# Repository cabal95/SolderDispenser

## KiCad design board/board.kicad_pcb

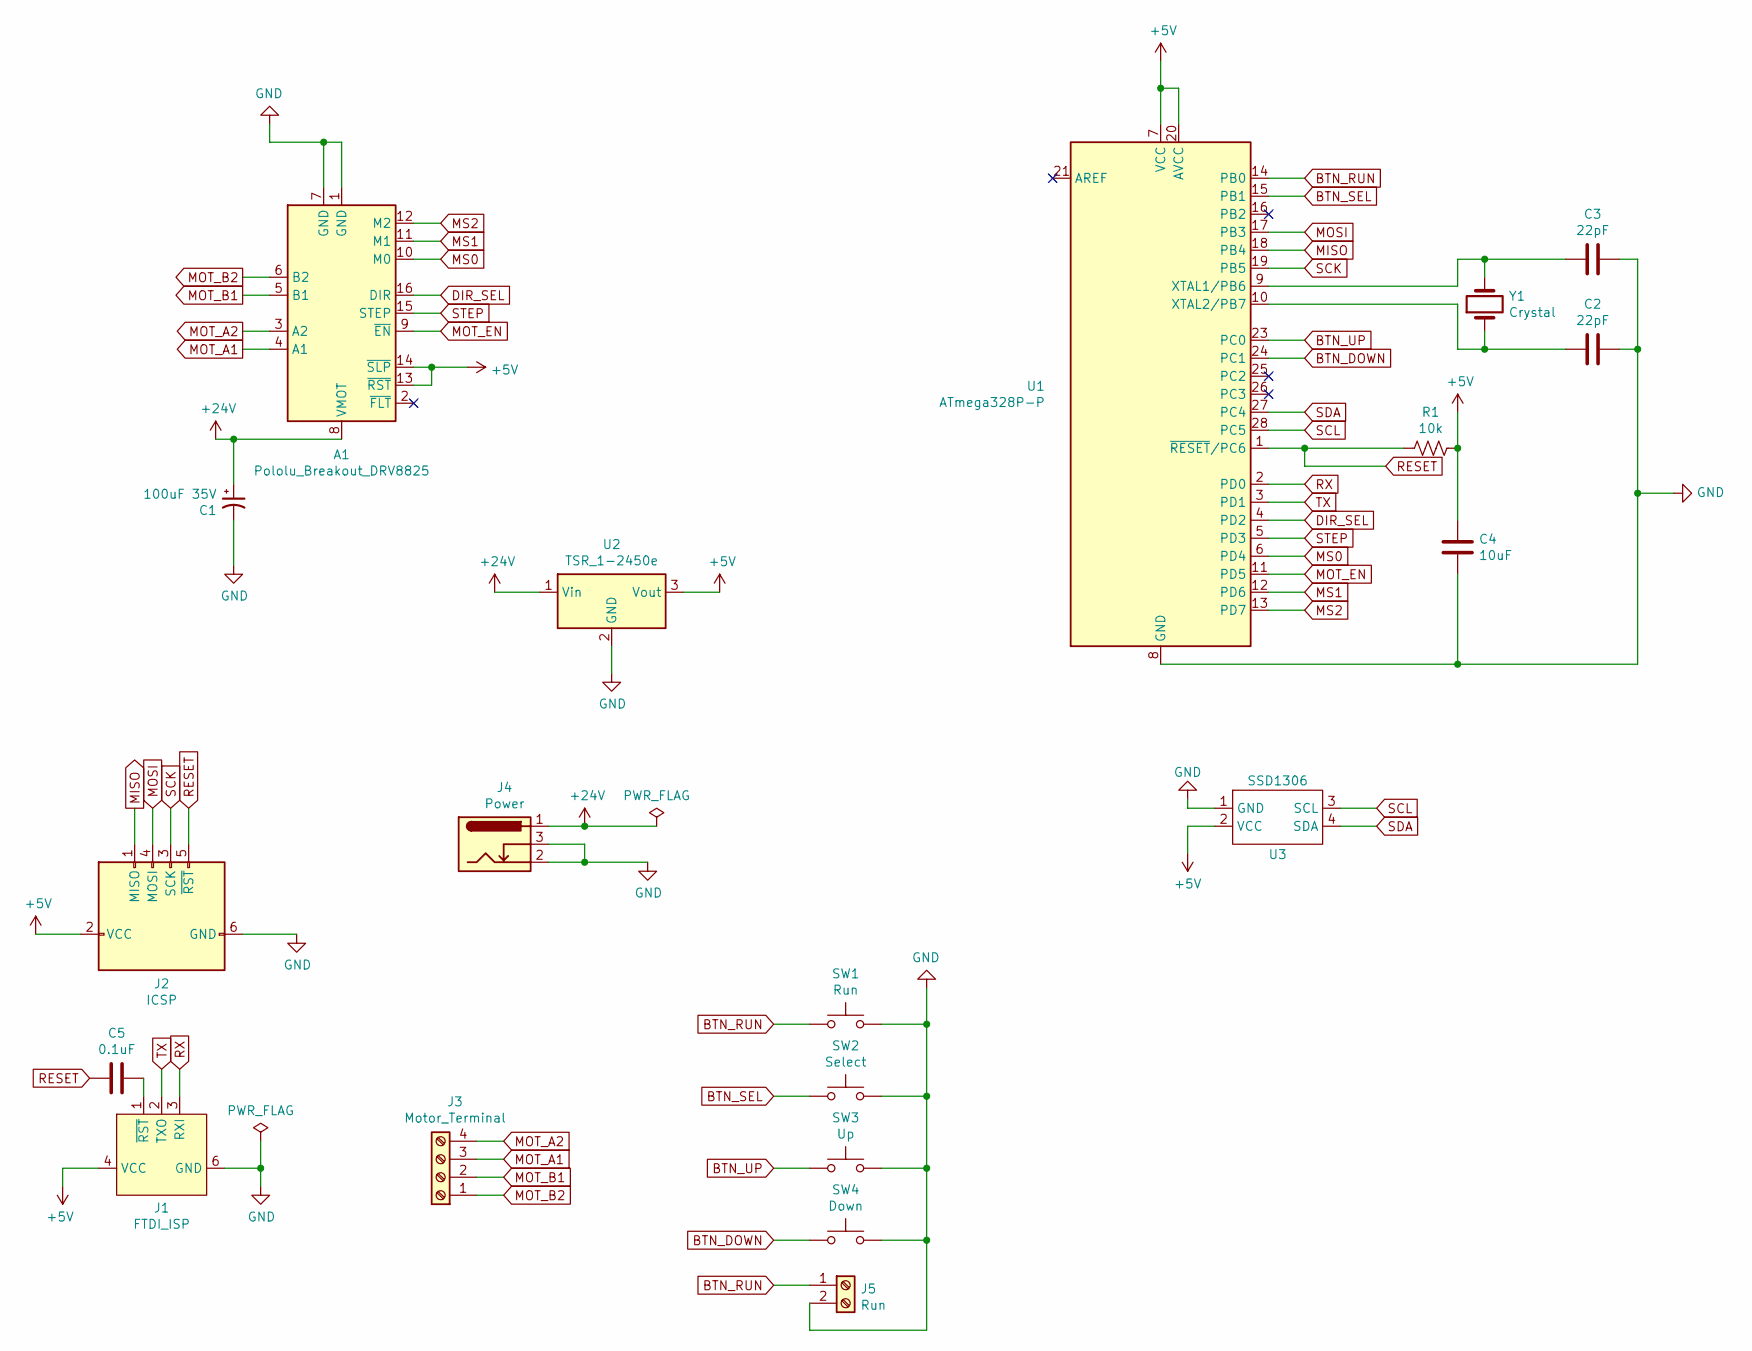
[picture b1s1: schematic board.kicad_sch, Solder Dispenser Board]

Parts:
A1: Pololu_Breakout_DRV8825; Pololu_Breakout-16_15.2x20.3mm
C1: 100uF 35V; CP_Radial_D6.3mm_P2.50mm
C2, C3: 22pF; C_Disc_D6.0mm_W2.5mm_P5.00mm
C4: 10uF; CP_Radial_D5.0mm_P2.00mm
C5: 0.1uF; C_Disc_D3.4mm_W2.1mm_P2.50mm
J1: FTDI_ISP; PinHeader_1x06_P2.54mm_Vertical
J2: ICSP; PinHeader_2x03_P2.54mm_Vertical
J3: Motor_Terminal; TerminalBlock_Phoenix_MKDS-1,5-4-5.08_1x04_P5.08mm_Horizont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
J4: Power; BarrelJack_Horizontal
J5: Run; TerminalBlock_Phoenix_MKDS-1,5-2-5.08_1x02_P5.08mm_Horizont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
R1: 10k; R_Axial_DIN0207_L6.3mm_D2.5mm_P10.16mm_Horizontal
SW1: Run; SW_PUSH_6mm_H5mm
SW2: Select; SW_PUSH_6mm_H5mm
SW3: Up; SW_PUSH_6mm_H5mm
SW4: Down; SW_PUSH_6mm_H5mm
U1: ATmega328P-P; DIP-28_W7.62mm
U2: TSR_1-2450e; Converter_DCDC_TRACO_TSR-1_THT
U3: SSD1306; PinHeader_1x04_P2.54mm_Vertical
Y1: Crystal; Crystal_HC49-U_Vertical

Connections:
+5V: A1.13 (~RST), A1.14 (~SLP), C4.1, J1.4 (VCC), J2.2 (VCC), R1.2, U1.7 (VCC), U1.20 (AVCC), U2.3 (Vout), U3.2 (VCC)
+24V: A1.8 (VMOT), C1.1, J4.1, U2.1 (Vin)
BTN_DOWN: SW4.1, U1.24 (PC1)
BTN_RUN: J5.1, SW1.1, U1.14 (PB0)
BTN_SEL: SW2.1, U1.15 (PB1)
BTN_UP: SW3.1, U1.23 (PC0)
DIR_SEL: A1.16 (DIR), U1.4 (PD2)
GND: A1.1 (GND), A1.7 (GND), C1.2, C2.2, C3.2, C4.2, J1.6 (GND), J2.6 (GND), J4.2, J4.3, J5.2, SW1.2, SW2.2, SW3.2, SW4.2, U1.8 (GND), U1.22 (GND), U2.2 (GND), U3.1 (GND)
MISO: J2.1 (MISO), U1.18 (PB4)
MOSI: J2.4 (MOSI), U1.17 (PB3)
MOT_A1: A1.4 (A1), J3.3
MOT_A2: A1.3 (A2), J3.4
MOT_B1: A1.5 (B1), J3.2
MOT_B2: A1.6 (B2), J3.1
MOT_EN: A1.9 (~EN), U1.11 (PD5)
MS0: A1.10 (M0), U1.6 (PD4)
MS1: A1.11 (M1), U1.12 (PD6)
MS2: A1.12 (M2), U1.13 (PD7)
unnamed: C2.1, U1.10 (XTAL2/PB7), Y1.1
unnamed: C3.1, U1.9 (XTAL1/PB6), Y1.2
unnamed: C5.2, J1.1 (~RST)
RESET: C5.1, J2.5 (~RST), R1.1, U1.1 (~RESET~/PC6)
RX: J1.3 (RXI), U1.2 (PD0)
SCK: J2.3 (SCK), U1.19 (PB5)
SCL: U1.28 (PC5), U3.3 (SCL)
SDA: U1.27 (PC4), U3.4 (SDA)
STEP: A1.15 (STEP), U1.5 (PD3)
TX: J1.2 (TXO), U1.3 (PD1)

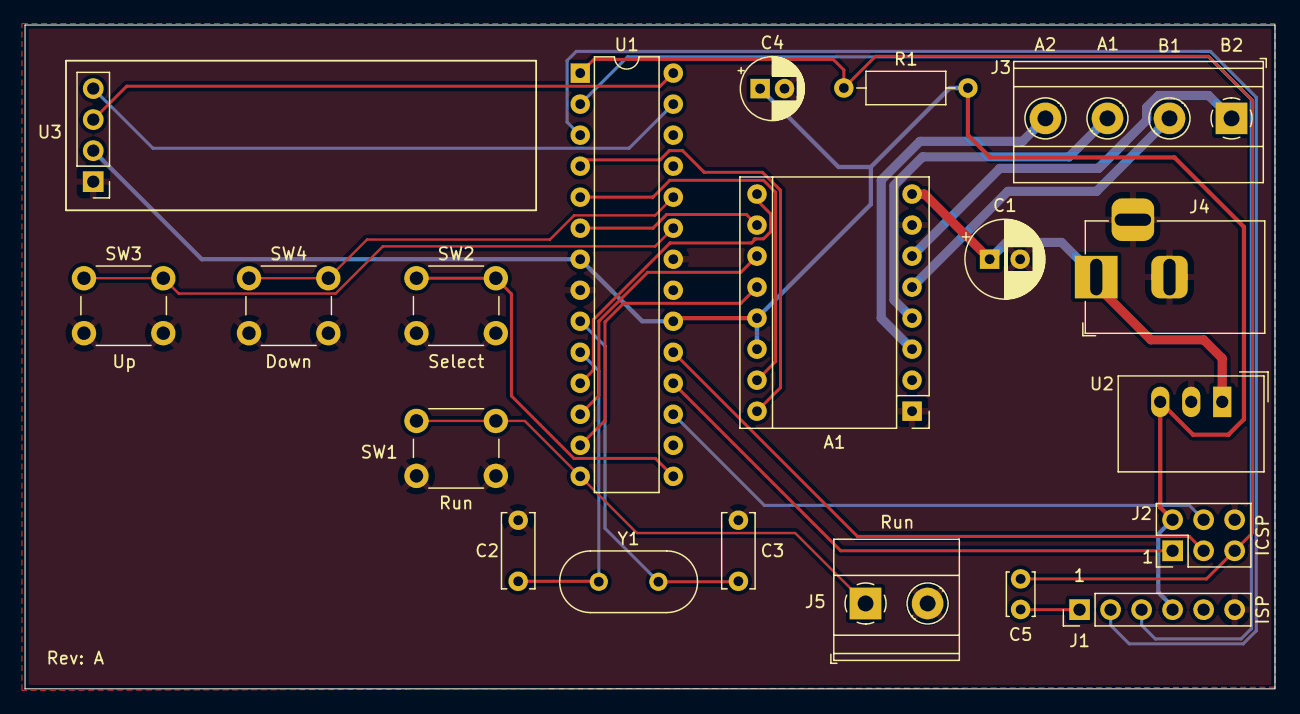
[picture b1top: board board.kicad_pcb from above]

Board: 2 copper layers, 102.4 x 54.4 mm, 20 parts (0 on the bottom side), 28 nets.

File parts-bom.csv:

Part,Manufacturer,Part Number,Description,Quantity,Unit Price,Link
C1,Nichicon,UVR1V101MED1TD,100uF 20% 35V Radial Capacitor,1,$0.30,https://www.digikey.com/en/products/detail/nichicon/UVR1V101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
"C2,C3",Vishay Beyschlag,S220K25SL0N63L6R,22pF ceramic disc capacitor 1kV,2,$0.36,https://www.digikey.com/en/products/detail/vishay-beyschlag-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
C4,Nichicon,USR1H100MDD,10uF 20% 50V Radial Capacitor,1,$0.27,https://www.digikey.com/en/products/detail/nichicon/USR1H100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
C5,Vishay Beyschlag,K104Z15Y5VF53L2,0.1uF 50V ceramic disc capacitor Y5V,1,$0.28,https://www.digikey.com/en/products/detail/vishay-beyschlag-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
J1,Amphenol ICC (FCI),68000-406HLF,1x6 Male Header Pin,1,$0.26,https://www.digikey.com/en/products/detail/amphenol-icc-fci/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
J2,Amphenol ICC (FCI),68602-406HLF,2x3 Male Header Pin,1,$0.26,https://www.digikey.com/en/products/detail/amphenol-icc-fci/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
J3,Phoenix Contact,1715747,4 position terminal block header 5.08mm,1,$2.60,https://www.digikey.com/en/products/detail/phoenix-contact/1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
J4,Switchcraft Inc.,RAPC712BKZ,"DC barrel jack, 5.5mm x 2.5mm 100VDC@5A",1,$2.01,https://www.digikey.com/en/products/detail/switchcraft-inc/R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
J5,Phoenix Contact,1715721,2 position terminal block header 5.08mm,1,$1.33,https://www.digikey.com/en/products/detail/phoenix-contact/1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
R1,Yageo,CFR-25JB-52-10K,10K resistor,1,$0.10,https://www.digikey.com/en/products/detail/yageo/CFR-25JB-52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
RV1,Amphenol Piher Sensing Systems,PT10LV10-103A2020-PM-S,10K potentiometer,1,$0.46,https://www.digikey.com/en/products/detail/amphenol-piher-se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
"SW1,SW2,SW3,SW4",TE Connectivity,1825910-6,6x6mm round cap tactile switch,4,$0.10,https://www.digikey.com/en/products/detail/te-connectivity-a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
U1,Microchip Technology,ATMEGA328-PU,Micro controller,1,$2.30,https://www.digikey.com/en/products/detail/microchip-technol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
U2,Traco Power,TSR 1-2450E,24v to 5v switching regulator,1,$5.81,https://www.digikey.com/en/products/detail/traco-power/TSR-1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
U3,MakerFocus,SSD1306 White,SSD1306 128x32 I2C 4-pin,1,$9.99,https://smile.amazon.com/gp/product/B079BN2J8V
Y1,ECS Inc.,ECS-160-S-4,16MHz crystal oscillator,1,$0.69,https://www.digikey.com/en/products/detail/ecs-inc/ECS-160-S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

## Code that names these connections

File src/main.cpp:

#include <Arduino.h>
#include <DRV8825.h>
#include "eventloop.h"
#include "timereventsource.h"
#include "buttoneventsource.h"
#include "ssd1306.h"
#include "fonts.h"
#include "menu.h"

#define MOTOR_MICROSTEP 4L
#define MOTOR_STEP_COUNT (200L * MOTOR_MICROSTEP)

#define BTN_RUN 8 /* Pin 14 */
#define BTN_SELECT 9 /* Pin 15 */
#define BTN_UP 14 /* Pin 23 */
#define BTN_DOWN 15 /* Pin 24 */
#define MOTOR_DIR 2 /* Pin 4 */
#define MOTOR_STEP 3 /* Pin 5 */
#define MOTOR_MS0 4 /* Pin 6 */
#define MOTOR_EN 6 /* Pin 11 */
#define MOTOR_MS1 7 /* Pin 12 */
#define MOTOR_MS2 8 /* Pin 13 */

EventLoop mainLoop;
Ssd1306 ssd = Ssd1306(&Wire, 0x3c);
Menu menu;
DRV8825 stepper = DRV8825(200, MOTOR_DIR, MOTOR_STEP);

void toggleLed();
void btnRunPressed();
void btnRunReleased();
void btnUpPressed();
void btnDownPressed();
void btnSelectPressed();

void setup()
{
    Serial.begin(9600);

    Wire.begin();
    ssd.begin();
    ssd.setFont(Font8x16, 8, 16);

    stepper.begin(1, MOTOR_MICROSTEP);

    menu.init(&ssd);

    ButtonEventSource *btnRun = new ButtonEventSource(BTN_RUN, false);
    btnRun->setPressedHandler(btnRunPressed);
    btnRun->setReleasedHandler(btnRunReleased);
    mainLoop.addEvent(btnRun);

    ButtonEventSource *btnUp = new ButtonEventSource(BTN_UP, false);
    btnUp->setPressedHandler(btnUpPressed);
    mainLoop.addEvent(btnUp);

    ButtonEventSource *btnDown = new ButtonEventSource(BTN_DOWN, false);
    btnDown->setPressedHandler(btnDownPressed);
    mainLoop.addEvent(btnDown);

    ButtonEventSource *btnSelect = new ButtonEventSource(BTN_SELECT, false);
    btnSelect->setPressedHandler(btnSelectPressed);
    mainLoop.addEvent(btnSelect);

    ssd.dimDisplay(true);
}

void loop()
{
    stepper.nextAction();
    mainLoop.runOnce();

    if (Serial.available() > 0)
    {
        int c = Serial.read();

        if (c == 'u')
        {
            menu.keyUp();
            Serial.println("Up");
        }
        else if (c == 'd')
        {
            menu.keyDown();
        }
        else if (c == 's')
        {
            menu.keySelect();
        }
    }
}

void btnRunPressed()
{
    if (menu.getMode() == DispenserMode::Step)
    {
        int steps = menu.getStepSize();

        if (menu.getDirection() == DispenserDirection::Backward)
        {
            steps = -steps;
        }

        stepper.setRPM(60);
        stepper.startMove(steps);
    }
    else
    {
        long steps = 100 * MOTOR_STEP_COUNT;

        if (menu.getDirection() == DispenserDirection::Backward)
        {
            steps = -steps;
        }

        stepper.setRPM(menu.getDriveSpeed() / (float)MOTOR_STEP_COUNT * 60.0);
        stepper.startMove(steps);
    }
}

void btnRunReleased()
{
    if (menu.getMode() == DispenserMode::Drive)
    {
        stepper.stop();
    }
}

void btnUpPressed()
{
    menu.keyUp();
}

void btnDownPressed()
{
    menu.keyDown();
}

void btnSelectPressed()
{
    menu.keySelect();
}

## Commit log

2021-02-08 - Initial Import of source code.
2021-02-09 Renamed RunLoop to EventLoop and removed template functionality on LinkedListItem to save on memory.
2021-02-09 Continue renaming spree.
2021-02-09 Make menu somewhat functional for demo purposes.
2021-02-11 - Updates to the menu interface.
2021-02-11 - Implement motor controls.
2021-03-25 - Updates to make use of an SSD1306 OLED display instead of the bulky LCD.
2021-03-25 - Initial PCB designs.
2021-03-25 Remove old LiquidCrystal library that is no longer used.
2021-03-25 Added support for the select button.
2021-03-25 Added 8x13 and 8x16 font options.
2021-03-25 Better dimming control.
2021-03-25 Added reference document for SSD1306.
2021-03-27 Updted PCB for new SSD1306 display.
2021-03-27 Update parts, enable drill files.
2021-03-28 Fixed an overlapping trace that got missed in last DRC.
2021-04-04 Fixed incorrect +5v to GND connection.
2021-04-04 Added new platform for direct ATmega328 chip.
2022-07-20 Random updates.
